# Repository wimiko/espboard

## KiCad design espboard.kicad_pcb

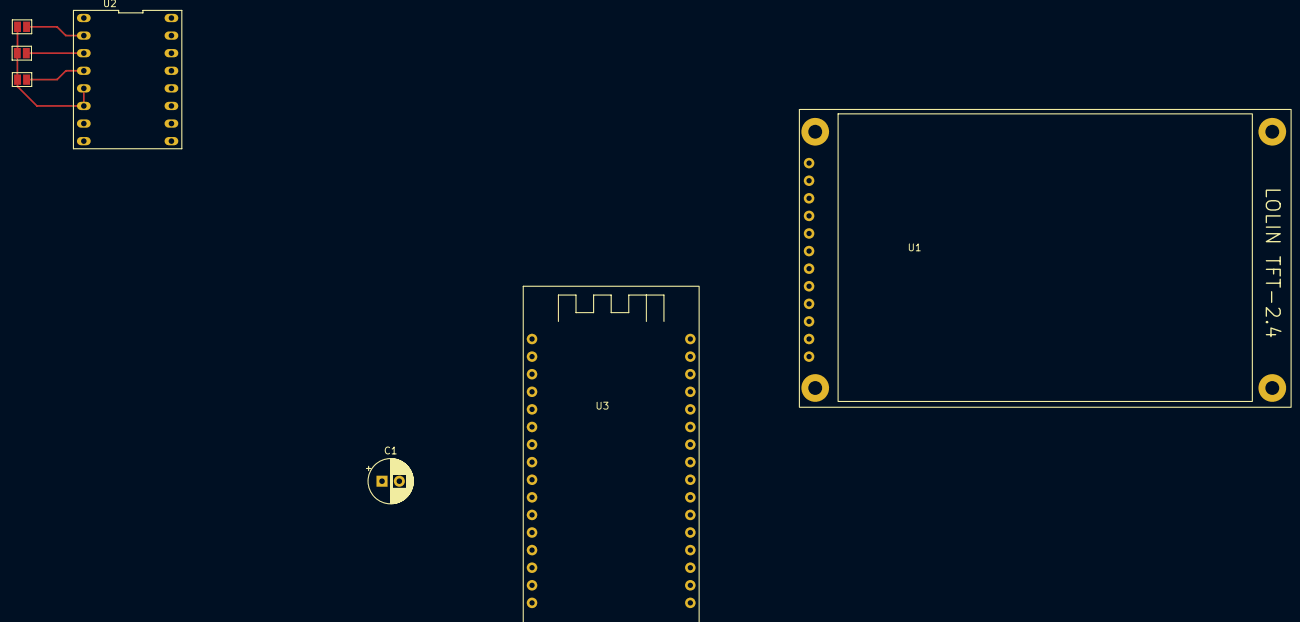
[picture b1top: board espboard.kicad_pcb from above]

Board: 2 copper layers, 8 parts (0 on the bottom side), 12 nets.

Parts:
C1: C_Polarized; CP_Radial_D6.3mm_P2.50mm
JP1, JP2, JP3: SolderJumper_2_Open; SolderJumper-2_P1.3mm_Open_Pad1.0x1.5mm
Ref**: Val**; baast_kicad_logo
U1: lolin_tft-2.4
U2: a4988_module
U3: lolin_d32

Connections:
+3.3V: JP1.1 (A), JP2.1 (A), JP3.1 (A), U1.3 (3V3), U2.5 (RST_N), U2.6 (SLP_N), U2.10 (VDD)
/SPI_CSN_TFT: U1.10 (TFT_CS), U3.A6 (IO32)
/SPI_CSN_TS: U1.4 (TS_IRQ), U1.6 (TS_CS), U3.B9 (IO18)
/SPI_MISO: U1.7 (MISO), U3.B7 (IO19)
/SPI_MOSI: U1.8 (MOSI), U3.B6 (IO21)
/SPI_SCK: U1.9 (SCK), U3.A7 (IO33)
/TFT_DC: U1.11 (TFT_DC), U3.B3 (IO22)
/TFT_RST: U1.12 (TFT_RST), U3.B2 (IO23)
GND: C1.2, U1.1 (GND), U2.9 (GND), U2.15 (GND), U3.A14 (EN), U3.B1 (GND), U3.B16 (GND)
unnamed: JP1.2 (B), U2.2 (MS1)
unnamed: JP2.2 (B), U2.3 (MS2)
unnamed: JP3.2 (B), U2.4 (MS3)

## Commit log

2023-07-24 initial version
2023-07-24 add .zip to ignore
